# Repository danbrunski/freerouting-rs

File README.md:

# freerouting-rs

A Rust port of [Freerouting](https://github.com/freerouting/freerouting), the open-source
Specctra DSN/SES autorouter for printed circuit boards. The port has three parts:
- `freerouting-rs`, a command line that routes a board;
- `freerouting-gui`, a desktop app for viewing, routing and editing;
- a KiCad plugin that routes the board open in KiCad's PCB editor.

It runs natively on Windows, macOS, Linux and WSL, without a Java runtime.

The port follows the Java code closely, so a board routes the same way. On the 140-board parity
gate, 135 boards produce a session byte-identical to Java's (Freerouting pinned at `a773a70ec`).
Every intended difference is listed in [docs/DIVERGENCES.md](docs/DIVERGENCES.md).

Status: version 0.1.0.
- The router, the desktop app and the KiCad plugin all work end to end.
- There is no published release yet; build from source as below.

## What it does better than the Java version

**Two routing profiles.** **Enhanced**, the default, routes with the improvements over Java that
a measurement has accepted; **Legacy** gives results identical to Java Freerouting. Below the
profile every stage (fanout, net ordering, connection router, rip-up policy, optimizer, the
special stages) and every option can still be set on its own. Pick one with `--profile legacy`
on the command line, the Profile selector in the desktop app's autoroute settings, or the
Profile choice in the KiCad plugin's dialog.

Enhanced changes three things so far, each accepted by a measurement on real boards
([docs/DIVERGENCES.md](docs/DIVERGENCES.md), "Profile `enhanced`"):
- **No traces on power layers.** Vias still land in their net's plane.
- **Neck-down when a connection fails.** A failed connection is retried with traces down to
  300 µm, so a board can keep its Board Setup class widths. Full width is kept wherever the
  first attempt fits.
- **Vias take their net class's clearance**, as KiCad checks them, where Java uses the via
  rule's.

**Java's bugs, fixed one switch at a time.** The port kept Java's bugs so that Legacy matches
Java. The ones no board reaches are now fixed outright. Each of the others has a fix behind
`router.java_quirks.<id>`; unset means Java's behaviour, and Legacy keeps every one. A fix
joins Enhanced once its measurement accepts it, including a fix that changes nothing on the
measured boards: 37 of them so far (the maze search, the fanout, shove, pull-tight, the batch
optimizer, the any-angle room graph, the geometry cutouts, the DSN and SES readers, the reports and interactive
editing). `--router.java_quirks.<id>=true` brings one
bug back. Options that won only on one kind of board are offered as **Experimental**, with that
board class in their help text.

**Speed**
- **No JVM.** Each tool is one native executable that starts in milliseconds. Java spends about
  3 s on start-up and class loading before routing begins. Small boards therefore finish 7× to
  160× sooner end to end: for example 0.04 s against 3.2 s, and 0.54 s against 3.9 s.
- **Large boards route at about Java's speed today.** On the 11 benchmark boards where Java takes
  at least 10 s:
  - the median board is 1.16× faster than Java, with interf_u up to 4.6× faster;
  - the largest boards, with many connections, run at 0.77× to 0.92× of Java's speed;
  - so in total Rust takes about 9 % longer.

  These timings were taken on a busy machine, so they are rough
  ([docs/roadmap/performance.md](docs/roadmap/performance.md)). Getting clearly ahead, with a
  target of 3× on large boards, is the performance roadmap's job.
- **A parallel optimizer that is also reproducible.** Java's multi-threaded optimizer gives
  different results from run to run. Here the thread count changes nothing in the output, and
  the work still scales: the optimizer on DAC2020 bm10 takes 53 s on one thread and 10 s on
  eight, with a byte-identical session on every run.

**For KiCad users**
- **Reads and writes `.kicad_pcb` directly.** Java only reads Specctra DSN; given a KiCad board it
  reports "Unknown file type".
- **A plugin with live progress.**
  - The options sit on three tabs (Route, Board and DSN, Advanced), with the buttons always in
    view.
  - "Stop and keep result" finishes the current step and imports the best board so far. "Abort"
    imports nothing.
  - "Route in GUI" watches the routing in the desktop app.
  - Rule areas are fixed up before routing. Optional fix-ups (class widths, fixed or dropped
    pours, opened plane layers, edge and pad clearances as keepouts) reproduce canary's export on
    either board input, and presets save a set of options for reuse.
  - It routes a snapshot of the open board through the router's own `.kicad_pcb` reader by default,
    and uses KiCad's DSN export instead when the reader refuses the board, or when you pick it
    (the Legacy profile defaults to the DSN, as Java's plugin does).
  - Net and part names outside ASCII round-trip intact (Java's plugin strips them).
  - A version check catches a mismatched router.
  - Its plugin-manager package, not yet published, carries the executables for Windows, macOS
    and Linux.

**For scripts and tools**
- **The CLI accepts Java's flags and adds:**
  - `--progress json` and `--result-json` for machine-readable progress and results;
  - `--version`, `--capabilities`, `--threads` and `--timeout`;
  - `--profile legacy|enhanced`, `--list-stages` (the stages, their ids and options) and
    `--dump-settings` (every effective setting and where it came from);
  - a stop request on standard input that keeps the best result so far;
  - distinct exit codes.
- **No half-written files.** An output file is written whole or not at all, and never as 0 bytes.
- **Diagnostics.** A report says why a connection cannot be routed, not only that it wasn't.

**The desktop app**
- **The board is drawn on the GPU** with wgpu. A synthetic board of 5.6 million triangles stays
  under 2 ms per frame (p95), and the view redraws live while the autorouter runs.
- **Interactive routing and editing**, undo and redo, the rules dialogs and the Info lists, all
  ported from Java's GUI.

**Still in progress.** More candidates are being measured for Enhanced. The stages ported from
KiCadRoutingTools can be picked in the command line, the app and the plugin, but none is on by
default: length matching (`krt-meander`), BGA and QFN fanout (`krt-bga-escape`,
`krt-qfn-escape`), and coupled differential pairs (`krt-diffpair`, Experimental: it helps boards
with one or a few pairs on a shared signal layer). The KiCadRoutingTools grid router and bus
routing were measured and removed. See [docs/roadmap/](docs/roadmap/).

## Install the KiCad plugin

One command builds the router and the app and installs the plugin into KiCad:

```
python tools/install_plugin.py
```

Any Python 3.8 or newer works, KiCad's own included. Before building, it checks the machine and
offers to fix what is missing, asking first each time:
- **Rust:**
  - Windows: rustup through `winget`;
  - Linux and macOS: the rustup.rs script;
  - any system: `rustup update` when the installed Rust is older than the workspace needs.
- **A linker:**
  - Windows: Visual Studio's C++ build tools, or, without them, the `windows-gnu` toolchain with
    WinLibs' mingw-w64 (it finds an existing install and puts it on the PATH for the build);
  - Linux: a C compiler, from the distribution's packages (apt, dnf, pacman, zypper);
  - macOS: the Xcode command line tools.
- **The viewer's libraries on Linux:** xkbcommon, and Vulkan or EGL.
- **Before the build starts:**
  - KiCad's user folder, where KiCad itself looks: under `KICAD_DOCUMENTS_HOME` when set, else
    Windows' Documents folder (asked of Windows, also from WSL, so one that OneDrive or a
    redirection moved to another drive is found), `~/Documents` on macOS, and `XDG_DATA_HOME` or
    the Flatpak's folder on Linux;
  - enough free disk space;
  - on Windows, a viewer or router still running, since Windows locks a running exe.

Useful options:

| Option | What it does |
|---|---|
| `--check` | Report what is there and what is missing; change nothing |
| `--yes` | Apply every fix offered without asking |
| `--no-setup` | Never install anything; stop on a problem |
| `--skip-build` | Install the executables already built |
| `--windows-kicad` | From WSL: install into the Windows KiCad, which then runs this Linux build through WSL |
| `--kicad-version 9.0` | Install into that KiCad version's folder instead of the newest |
| `--plugins-dir DIR` | Install into DIR; with `--windows-kicad`, a Windows path such as `D:\Documents\KiCad\10.0\scripting\plugins` works too |
| `--keep-pcm` | Passed to `kicad-plugin/install.py` |

Then, in KiCad's PCB editor: Tools > External Plugins > Refresh Plugins. No restart is needed.
The plugin's own documentation: [kicad-plugin/README.md](kicad-plugin/README.md).

## Build and run by hand

```
cargo build --release -p freerouting-cli -p freerouting-gui
target/release/freerouting-rs -de board.dsn -do board.ses               # route
target/release/freerouting-rs -de board.kicad_pcb -do routed.kicad_pcb  # a KiCad board, directly
target/release/freerouting-gui fixtures/Issue754-avionics_hub.dsn       # the desktop app
```

`freerouting-rs --help` lists every option. The command is `freerouting-rs`, not Java
Freerouting's `freerouting`, so the two can be installed side by side.

The app opens a `.dsn` (optionally with its `.ses` as a second argument) or a `.kicad_pcb`, from
the command line, from File > Open, or by dropping the file on the window. Scroll to zoom, drag to
pan, `F` to fit the board, `1`–`9` to bring a layer to the front.

On Linux the app needs the usual X11 or Wayland libraries (`libxkbcommon-x11`, plus a Vulkan or
OpenGL driver). Under WSL it runs through WSLg.

## Layout

| Crate | Purpose |
| --- | --- |
| `freerouting-geometry` | Planar geometry with exact integer and rational math |
| `freerouting-dsn` | Specctra DSN, SES and rules parsing and writing |
| `freerouting-kicad` | Direct `.kicad_pcb` reading and writing |
| `freerouting` | The routing engine: board, rules, DRC, autorouter, optimizer |
| `freerouting-krt` | Routing stages ported from KiCadRoutingTools |
| `freerouting-stages` | The full stage registry (engine plus KRT stages) the CLI and GUI route with |
| `freerouting-cli` | The `freerouting-rs` command line |
| `freerouting-gui` | The `freerouting-gui` desktop app (egui/eframe, wgpu) |
| `freerouting-dev` | Developer tools: benchmarks, parity checks, the board corpus |

How the port maps the Java modules: [docs/PORT_PLAN.md](docs/PORT_PLAN.md).

## License

GPL-3.0, the same as upstream Freerouting, since this is a derivative work.

Portions are ported from KiCadRoutingTools (MIT, Copyright (c) 2026
drandyhaas). Its licence text is in `LICENSES/MIT-KiCadRoutingTools.txt` and
the sources are listed in `THIRD_PARTY_NOTICES.md`.

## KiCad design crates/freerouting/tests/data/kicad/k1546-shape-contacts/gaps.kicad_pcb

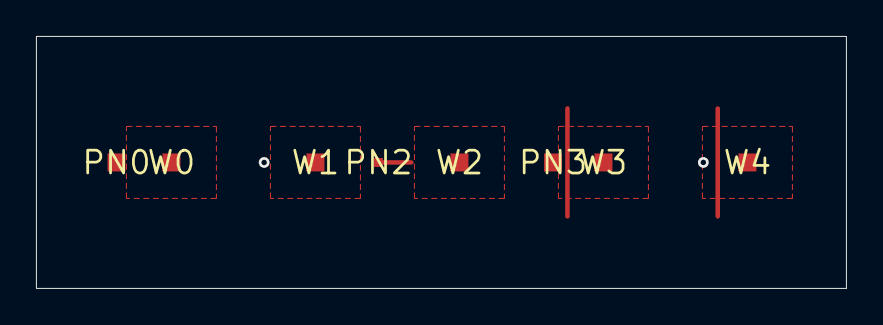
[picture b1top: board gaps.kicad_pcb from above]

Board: 2 copper layers, 45.0 x 14.0 mm, 8 parts (0 on the bottom side), 3 nets.

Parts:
PN0: x; PN0
PN2: x; PN2
PN3: x; PN3
W0: x; W0
W1: x; W1
W2: x; W2
W3: x; W3
W4: x; W4

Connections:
N0: PN0.1, W0.1
N2: PN2.1, W2.1
N3: PN3.1, W3.1

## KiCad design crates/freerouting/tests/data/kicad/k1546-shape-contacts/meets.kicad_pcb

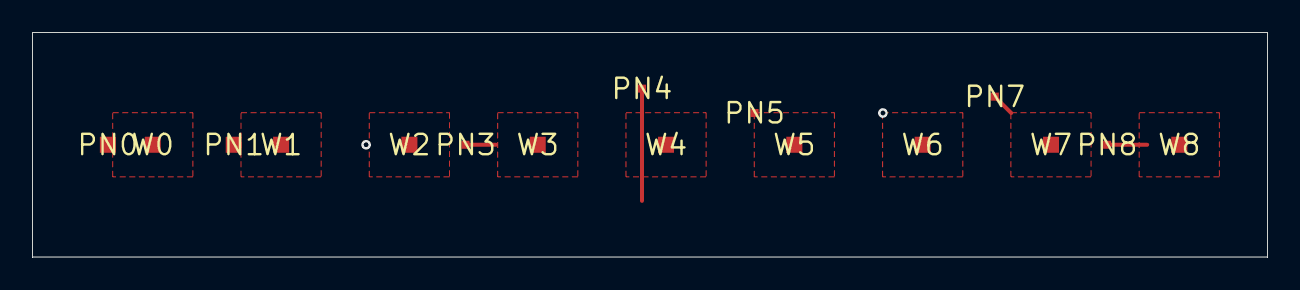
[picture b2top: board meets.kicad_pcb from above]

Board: 2 copper layers, 77.0 x 14.0 mm, 16 parts (0 on the bottom side), 7 nets.

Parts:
PN0: x; PN0
PN1: x; PN1
PN3: x; PN3
PN4: x; PN4
PN5: x; PN5
PN7: x; PN7
PN8: x; PN8
W0: x; W0
W1: x; W1
W2: x; W2
W3: x; W3
W4: x; W4
W5: x; W5
W6: x; W6
W7: x; W7
W8: x; W8

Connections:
N0: PN0.1, W0.1
N1: PN1.1, W1.1
N3: PN3.1, W3.1
N4: PN4.1, W4.1
N5: PN5.1, W5.1
N7: PN7.1, W7.1
N8: PN8.1, W8.1

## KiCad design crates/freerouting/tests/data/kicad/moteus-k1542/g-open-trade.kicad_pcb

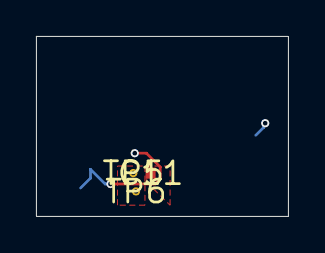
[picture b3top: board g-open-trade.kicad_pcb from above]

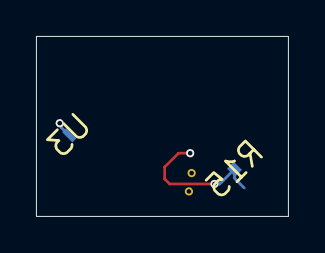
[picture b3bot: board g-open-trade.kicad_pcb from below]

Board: 4 copper layers, 14.0 x 10.0 mm, 5 parts (2 on the bottom side), 2 nets.

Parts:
C11: x; C11
R15: x; R15
TP5: x; TP5
TP6: x; TP6
U3: x; U3

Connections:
+3V: TP5.1, TP6.1
/Current Sense/FCUR3: R15.1, U3.1
